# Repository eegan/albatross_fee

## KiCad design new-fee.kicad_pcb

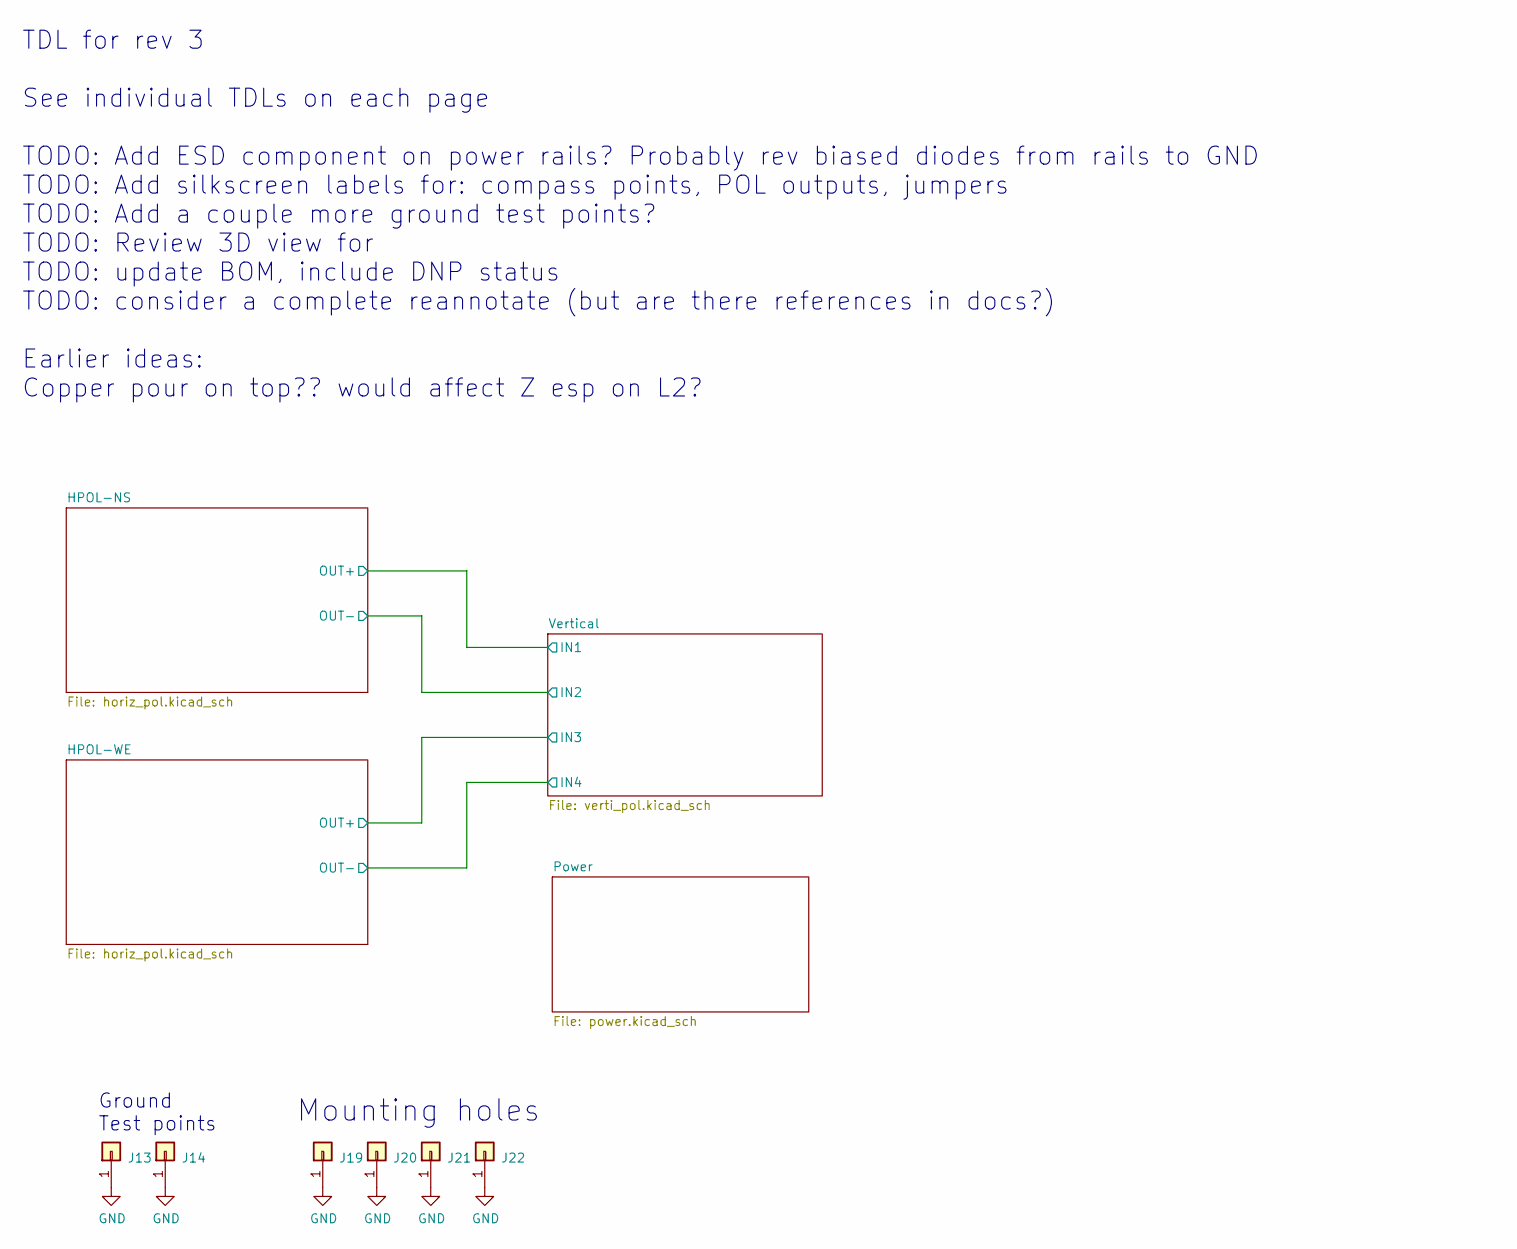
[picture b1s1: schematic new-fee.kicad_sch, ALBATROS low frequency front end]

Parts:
J13, J14: Conn_01x01; PinHeader_1x01_P2.54mm_Vertical
J19, J20, J21, J22: Conn_01x01; MountingHole_2.7mm_M2.5_Pad

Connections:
GND: J13.1, J14.1, J19.1, J20.1, J21.1, J22.1; also elsewhere on the board

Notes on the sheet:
Mounting holes
TDL for rev 3 See individual TDLs on each page TODO: Add ESD component on power rails? Probably rev biased diodes from rails to GND TODO: Add silkscreen labels for: compass points, POL outputs, jumpers TODO: Add a couple more ground test points? TODO: Review 3D view for TODO: update BOM, include DN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
Ground Test points

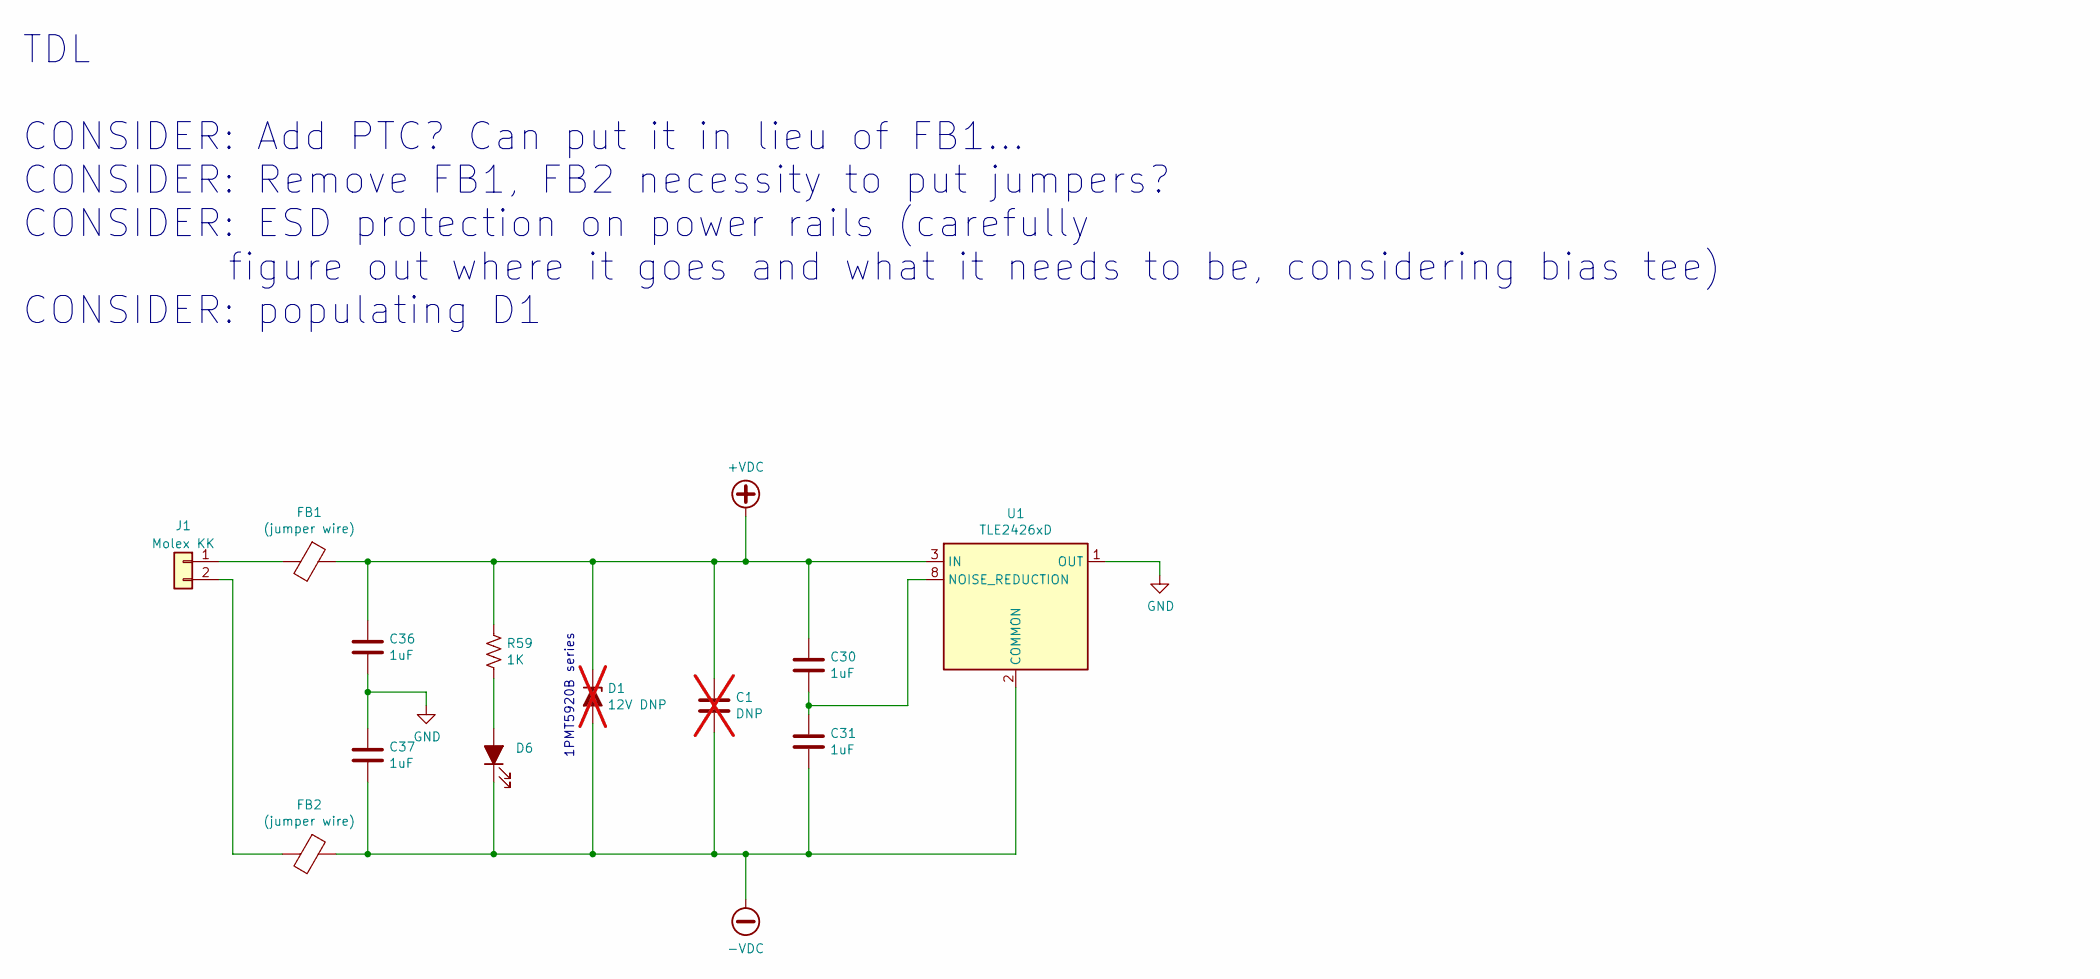
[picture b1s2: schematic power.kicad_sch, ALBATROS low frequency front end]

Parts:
C1: DNP; C_0603_1608Metric; not fitted
C30, C31, C36, C37: 1uF; C_0603_1608Metric; MPN CL10B105KA8NFNC
D1: 12V DNP; D_Powermite_AK; MPN 1PMT5927BT1G; not fitted
D6: LED_ALT; LED_0603_1608Metric; MPN 150060BS75000
FB1, FB2: (jumper wire); R_Axial_DIN0414_L11.9mm_D4.5mm_P25.40mm_Horizontal
J1: Molex KK; Molex_KK-254_AE-6410-02A_1x02_P2.54mm_Vertical; MPN 0022272021
R59: 1K; R_0603_1608Metric
U1: TLE2426xD; SOIC-8_3.9x4.9mm_P1.27mm; MPN TLE2426QDRG4Q1

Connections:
+VDC: C1.1, C30.1, C36.1, D1.1 (K), FB1.1, R59.1, U1.3 (IN); also elsewhere on the board
-VDC: C1.2, C31.2, C37.2, D1.2 (A), D6.1 (K), FB2.1, U1.2 (COMMON); also elsewhere on the board
GND: C36.2, C37.1, U1.1 (OUT); also elsewhere on the board
unnamed: D6.2 (A), R59.2
unnamed: FB1.2, J1.1
unnamed: FB2.2, J1.2
unnamed: C30.2, C31.1, U1.8 (NOISE_REDUCTION)

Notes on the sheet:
TDL CONSIDER: Add PTC? Can put it in lieu of FB1... CONSIDER: Remove FB1, FB2 necessity to put jumpers? CONSIDER: ESD protection on power rails (carefully figure out where it goes and what it needs to be, considering bias tee) CONSIDER: populating D1
1PMT5920B series

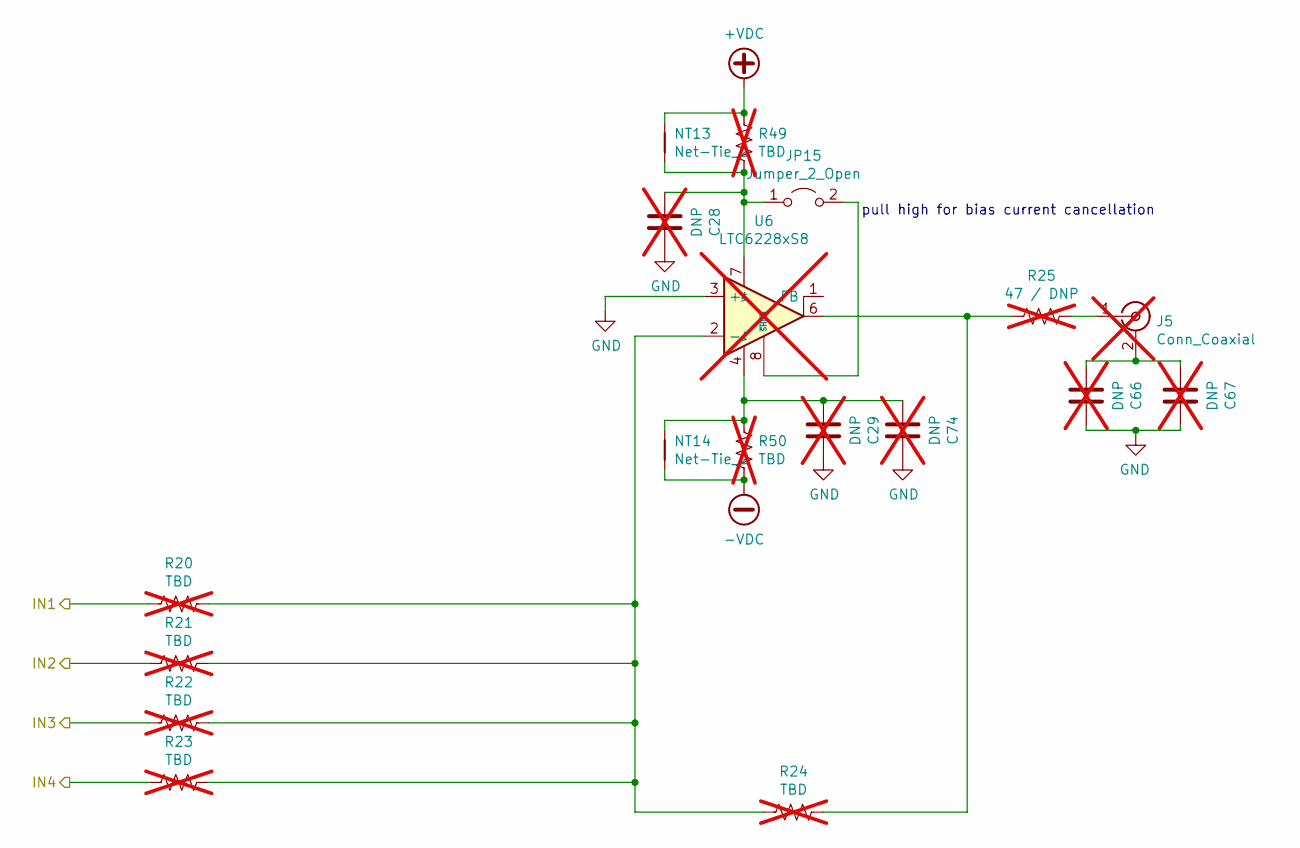
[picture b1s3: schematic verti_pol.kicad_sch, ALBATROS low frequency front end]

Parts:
C28, C29, C66, C67, C74: DNP; C_0603_1608Metric; not fitted
J5: Conn_Coaxial; SMA_Amphenol_901-144_Vertical; MPN 5-1814832-2; not fitted
JP15: Jumper_2_Open; SolderJumper-2_P1.3mm_Open_TrianglePad1.0x1.5mm
NT13, NT14: Net-Tie_2; NetTie-2_SMD_Pad0.5mm
R20, R21, R22, R23, R24, R49, R50: TBD; R_0603_1608Metric; not fitted
R25: 47 / DNP; R_0603_1608Metric; not fitted
U6: LTC6228xS8; SO-8_3.9x4.9mm_P1.27mm; not fitted

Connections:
+VDC: NT13.1, R49.2; also elsewhere on the board
-VDC: NT14.2, R50.1; also elsewhere on the board
/HPOL-NS/OUT+: R20.2; also elsewhere on the board
/HPOL-NS/OUT-: R21.2; also elsewhere on the board
/HPOL-WE/OUT+: R22.2; also elsewhere on the board
/HPOL-WE/OUT-: R23.2; also elsewhere on the board
GND: C28.1, C29.1, C66.1, C67.1, C74.1, U6.3 (+); also elsewhere on the board
unnamed: C29.2, C74.2, NT14.1, R50.2, U6.4 (V-), U6.5 (V-)
unnamed: C66.2, C67.2, J5.2 (Ext)
unnamed: J5.1 (In), R25.1
unnamed: C28.2, JP15.1 (A), NT13.2, R49.1, U6.7 (V+)
unnamed: JP15.2 (B), U6.8 (~SHDN)
unnamed: R24.1, R25.2, U6.6
unnamed: R20.1, R21.1, R22.1, R23.1, R24.2, U6.2 (-)

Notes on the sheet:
pull high for bias current cancellation

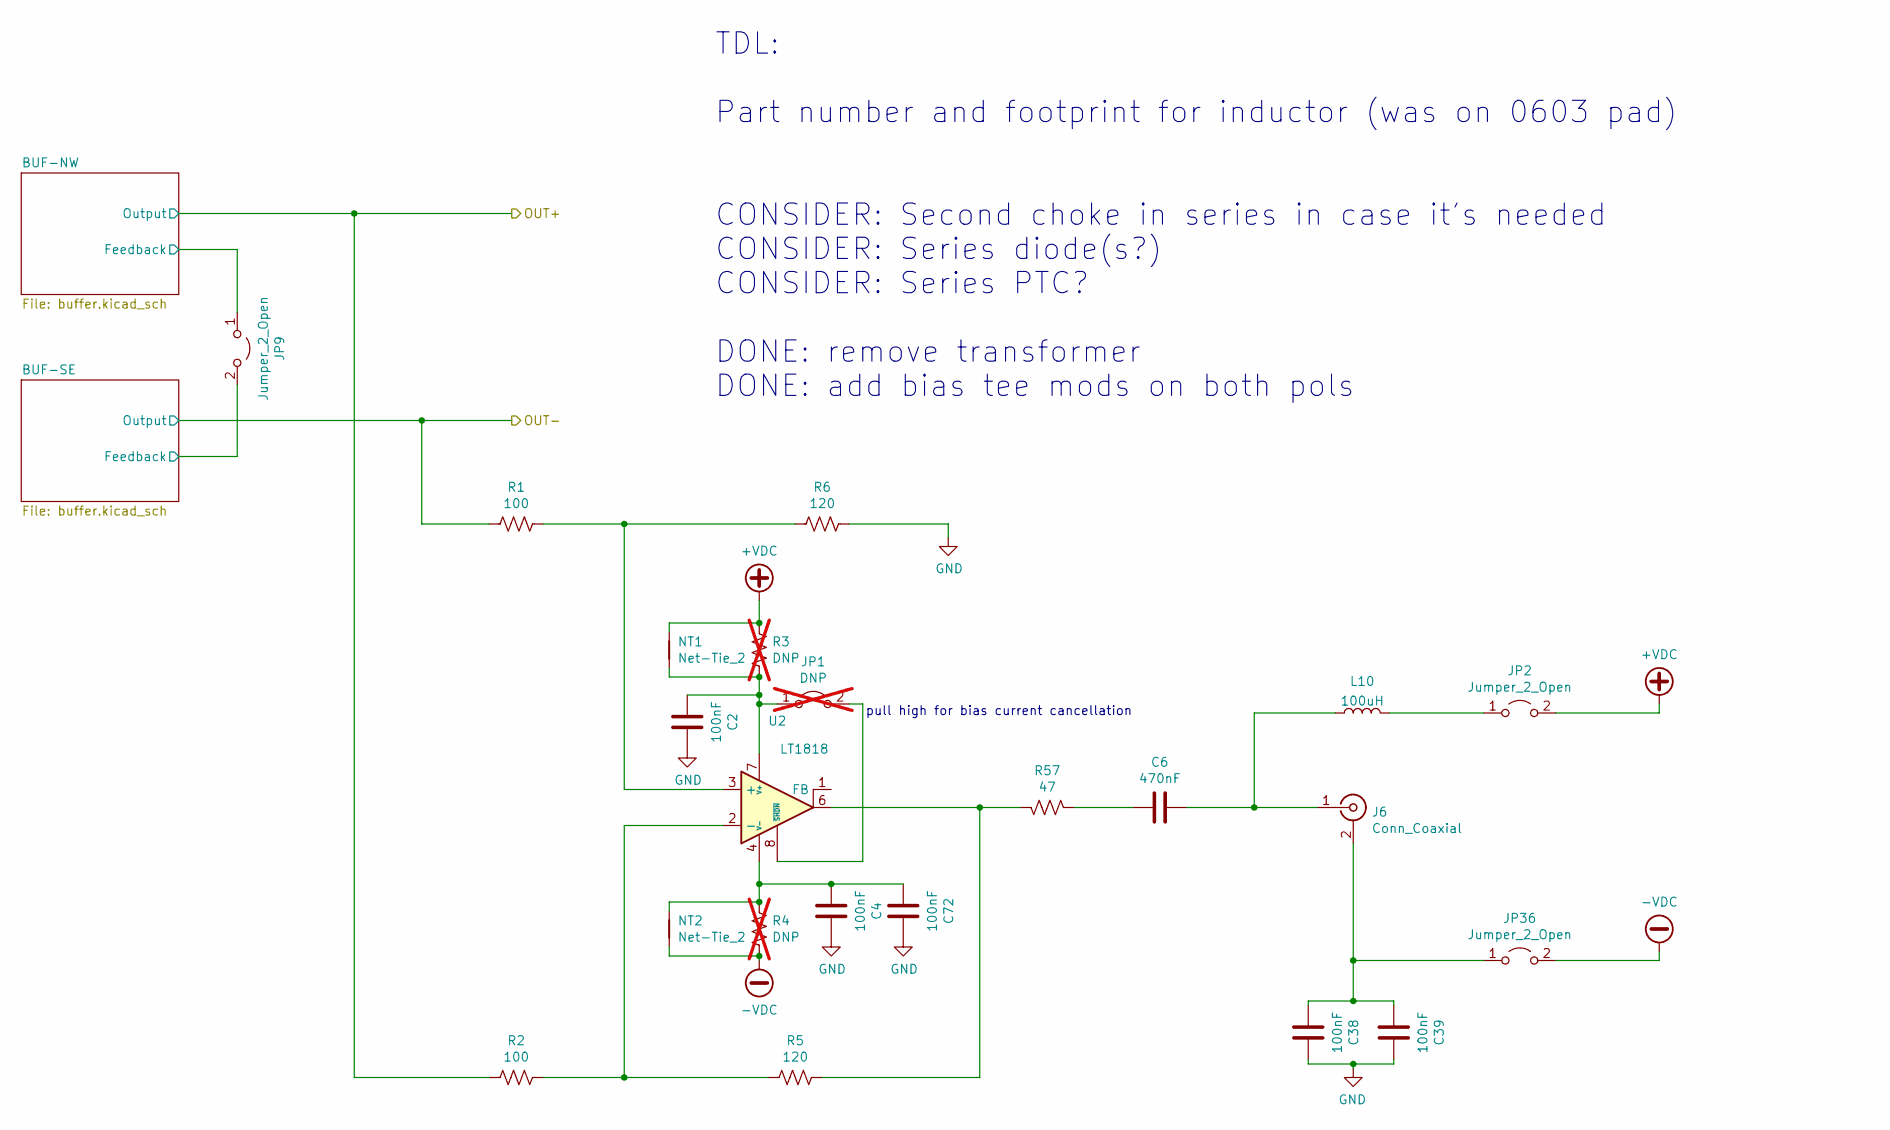
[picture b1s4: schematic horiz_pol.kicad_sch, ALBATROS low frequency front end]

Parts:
C2, C4, C38, C39, C72: 100nF; C_0603_1608Metric; MPN CL10B104KB8NNWC
C6: 470nF; C_0603_1608Metric; MPN CL10B474KA8NFNC
J6: Conn_Coaxial; SMA_Amphenol_901-144_Vertical; MPN 5-1814832-2
JP1: DNP; SolderJumper-2_P1.3mm_Open_TrianglePad1.0x1.5mm; not fitted
JP2, JP9, JP36: Jumper_2_Open; PinHeader_1x02_P2.54mm_Vertical
L10: 100uH; L_0603_1608Metric
NT1, NT2: Net-Tie_2; NetTie-2_SMD_Pad0.5mm
R1, R2: 100; R_0603_1608Metric
R3, R4: DNP; R_0603_1608Metric; not fitted
R5, R6: 120; R_0603_1608Metric
R57: 47; R_0603_1608Metric
U2: LT1818; SO-8_3.9x4.9mm_P1.27mm

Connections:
+VDC: JP2.2 (B), NT1.1, R3.2; also elsewhere on the board
-VDC: JP36.2 (B), NT2.2, R4.1; also elsewhere on the board
/HPOL-NS/BUF-NW/Feedback: JP9.1 (A); also elsewhere on the board
/HPOL-NS/BUF-SE/Feedback: JP9.2 (B); also elsewhere on the board
/HPOL-NS/OUT+: R2.2; also elsewhere on the board
/HPOL-NS/OUT-: R1.2; also elsewhere on the board
GND: C2.1, C4.1, C38.1, C39.1, C72.1, R6.1; also elsewhere on the board
unnamed: C4.2, C72.2, NT2.1, R4.2, U2.4 (V-), U2.5 (V-)
unnamed: C6.2, R57.2
unnamed: C38.2, C39.2, J6.2 (Ext), JP36.1 (A)
unnamed: C6.1, J6.1 (In), L10.1
unnamed: C2.2, JP1.1 (A), NT1.2, R3.1, U2.7 (V+)
unnamed: JP1.2 (B), U2.8 (~SHDN)
unnamed: JP2.1 (A), L10.2
unnamed: R5.1, R57.1, U2.6
unnamed: R1.1, R6.2, U2.3 (+)
unnamed: R2.1, R5.2, U2.2 (-)

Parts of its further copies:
C3: 470nF; C_0603_1608Metric; MPN CL10B474KA8NFNC
C5, C7, C52, C53, C73: 100nF; C_0603_1608Metric; MPN CL10B104KB8NNWC
J2: Conn_Coaxial; SMA_Amphenol_901-144_Vertical; MPN 5-1814832-2
JP3, JP21, JP37: Jumper_2_Open; PinHeader_1x02_P2.54mm_Vertical
JP4: DNP; SolderJumper-2_P1.3mm_Open_TrianglePad1.0x1.5mm; not fitted
L9: 100uH; L_0603_1608Metric
NT3, NT4: Net-Tie_2; NetTie-2_SMD_Pad0.5mm
R7, R8: 100; R_0603_1608Metric
R9, R10: DNP; R_0603_1608Metric; not fitted
R11, R12: 120; R_0603_1608Metric
R58: 47; R_0603_1608Metric
U3: LT1818; SO-8_3.9x4.9mm_P1.27mm

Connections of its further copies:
+VDC: JP3.2 (B), NT3.1, R9.2; also elsewhere on the board
-VDC: JP37.2 (B), NT4.2, R10.1; also elsewhere on the board
/HPOL-WE/BUF-NW/Feedback: JP21.1 (A); also elsewhere on the board
/HPOL-WE/BUF-SE/Feedback: JP21.2 (B); also elsewhere on the board
/HPOL-WE/OUT+: R8.2; also elsewhere on the board
/HPOL-WE/OUT-: R7.2; also elsewhere on the board
GND: C5.1, C7.1, C52.1, C53.1, C73.1, R12.1; also elsewhere on the board
unnamed: C3.2, R58.2
unnamed: C7.2, C73.2, NT4.1, R10.2, U3.4 (V-), U3.5 (V-)
unnamed: C52.2, C53.2, J2.2 (Ext), JP37.1 (A)
unnamed: C3.1, J2.1 (In), L9.1
unnamed: JP3.1 (A), L9.2
unnamed: C5.2, JP4.1 (A), NT3.2, R9.1, U3.7 (V+)
unnamed: JP4.2 (B), U3.8 (~SHDN)
unnamed: R11.1, R58.1, U3.6
unnamed: R7.1, R12.2, U3.3 (+)
unnamed: R8.1, R11.2, U3.2 (-)

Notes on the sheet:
TDL: Part number and footprint for inductor (was on 0603 pad) CONSIDER: Second choke in series in case it's needed CONSIDER: Series diode(s?) CONSIDER: Series PTC? DONE: remove transformer DONE: add bias tee mods on both pols
pull high for bias current cancellation

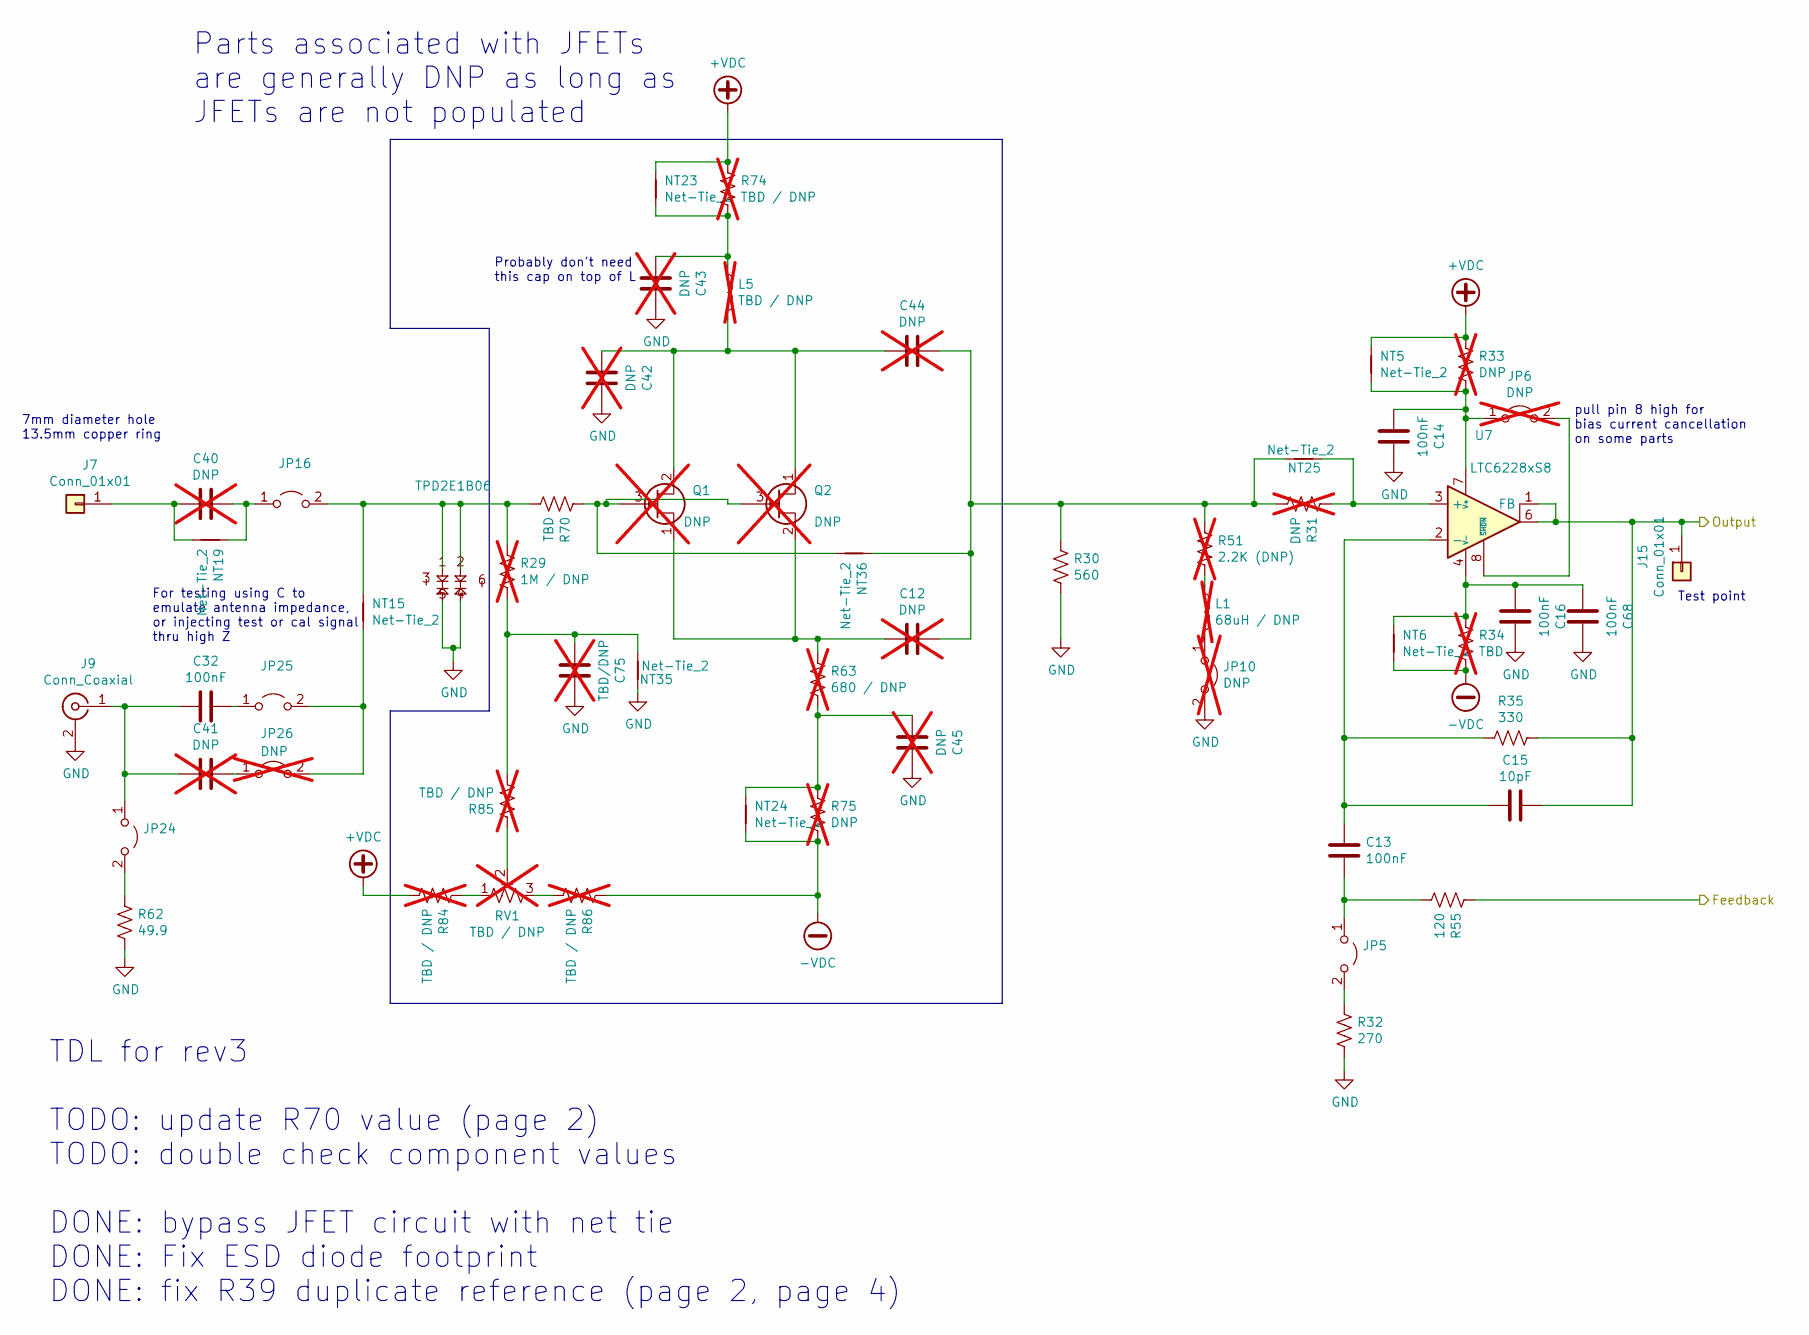
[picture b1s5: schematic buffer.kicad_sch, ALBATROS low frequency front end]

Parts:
C12, C40, C41, C42, C43, C44, C45: DNP; C_0603_1608Metric; not fitted
C13, C14, C16, C32, C68: 100nF; C_0603_1608Metric; MPN CL10B104KB8NNWC
C15: 10pF; C_0603_1608Metric; MPN CL10C100JB8NNNC
C75: TBD/DNP; C_0603_1608Metric; not fitted
D2: TPD2E1B06; SOT-563; MPN TPD2E1B06DRLR
J7: Conn_01x01; MountingHole_7.5mm
J9: Conn_Coaxial; SMA_Amphenol_132289_EdgeMount; MPN CONSMA020.062-G
J15: Conn_01x01; PinHeader_1x01_P2.54mm_Vertical
JP5, JP16, JP24, JP25: Jumper_2_Open; PinHeader_1x02_P2.54mm_Vertical
JP6: DNP; SolderJumper-2_P1.3mm_Open_TrianglePad1.0x1.5mm; not fitted
JP10, JP26: DNP; PinHeader_1x02_P2.54mm_Vertical; not fitted
L1: 68uH / DNP; L_Axial_L6.6mm_D2.7mm_P2.54mm_Vertical_Vishay_IM-2; not fitted
L5: TBD / DNP; L_0603_1608Metric; not fitted
NT5, NT6, NT15, NT19, NT23, NT24, NT25, NT35, NT36: Net-Tie_2; NetTie-2_SMD_Pad0.5mm
Q1, Q2: DNP; SOT-23; not fitted
R29: 1M / DNP; R_0603_1608Metric; not fitted
R30: 560; R_0603_1608Metric
R31, R33, R75: DNP; R_0603_1608Metric; not fitted
R32: 270; R_0603_1608Metric
R34: TBD; R_0603_1608Metric; not fitted
R35: 330; R_0603_1608Metric
R51: 2.2K (DNP); R_0603_1608Metric; not fitted
R55: 120; R_0603_1608Metric
R62: 49.9; R_0603_1608Metric
R63: 680 / DNP; R_0603_1608Metric; not fitted
R70: TBD; R_0603_1608Metric
R74, R84, R85, R86: TBD / DNP; R_0603_1608Metric; not fitted
RV1: TBD / DNP; Potentiometer_Bourns_3386C_Horizontal; not fitted
U7: LTC6228xS8; SO-8_3.9x4.9mm_P1.27mm

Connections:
+VDC: NT5.1, NT23.1, R33.2, R74.2, R84.1; also elsewhere on the board
-VDC: NT6.2, NT24.2, R34.1, R75.1, R86.2; also elsewhere on the board
/HPOL-NS/BUF-NW/Feedback: R55.2; also elsewhere on the board
/HPOL-NS/OUT+: C15.1, J15.1, R35.1, U7.1 (FB), U7.6; also elsewhere on the board
GND: C14.1, C16.1, C42.1, C43.1, C45.1, C68.1, C75.1, D2.4, D2.5, J9.2 (Ext), JP10.2 (B), NT35.1, R30.1, R32.1, R62.1; also elsewhere on the board
unnamed: C12.1, C44.1, NT25.2, NT36.1, R30.2, R31.1, R51.2
unnamed: C16.2, C68.2, NT6.1, R34.2, U7.4 (V-), U7.5 (V-)
unnamed: C43.2, L5.1, NT23.2, R74.1
unnamed: C45.2, NT24.1, R63.1, R75.2
unnamed: C75.2, NT35.2, R29.1, R85.1
unnamed: C40.2, J7.1, NT19.2
unnamed: C32.2, C41.2, J9.1 (In), JP24.1 (A)
unnamed: C13.1, JP5.1 (A), R55.1
unnamed: JP5.2 (B), R32.2
unnamed: C14.2, JP6.1 (A), NT5.2, R33.1, U7.7 (V+)
unnamed: JP6.2 (B), U7.8 (~SHDN)
unnamed: JP10.1 (A), L1.2
unnamed: C40.1, JP16.1 (A), NT19.1
unnamed: D2.1, D2.2, JP16.2 (B), NT15.1, R29.2, R70.1
unnamed: JP24.2 (B), R62.2
unnamed: C32.1, JP25.1 (A)
unnamed: JP25.2 (B), JP26.2 (B), NT15.2
unnamed: C41.1, JP26.1 (A)
unnamed: L1.1, R51.1
unnamed: C42.2, C44.2, L5.2, Q1.2 (D), Q2.1 (D)
unnamed: NT36.2, Q1.3 (G), Q2.3 (G), R70.2
unnamed: C12.2, Q1.1 (S), Q2.2 (S), R63.2
unnamed: R84.2, RV1.1
unnamed: R85.2, RV1.2
unnamed: R86.1, RV1.3
unnamed: NT25.1, R31.2, U7.3 (+)
unnamed: C13.2, C15.2, R35.2, U7.2 (-)

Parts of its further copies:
C8, C17, C23, C46, C47, C48, C49, C50, C51, C54, C55, C56, C57, C58, C59, C60, C61, C62, C63, C64, C65: DNP; C_0603_1608Metric; not fitted
C9, C10, C18, C19, C21, C22, C24, C25, C27, C33, C34, C35, C69, C70, C71: 100nF; C_0603_1608Metric; MPN CL10B104KB8NNWC
C11, C20, C26: 10pF; C_0603_1608Metric; MPN CL10C100JB8NNNC
C76, C77, C78: TBD/DNP; C_0603_1608Metric; not fitted
D3, D4, D5: TPD2E1B06; SOT-563; MPN TPD2E1B06DRLR
J3, J4, J8: Conn_01x01; MountingHole_7.5mm
J10, J11, J12: Conn_Coaxial; SMA_Amphenol_132289_EdgeMount; MPN CONSMA020.062-G
J16, J17, J18: Conn_01x01; PinHeader_1x01_P2.54mm_Vertical
JP7, JP11, JP13, JP17, JP18, JP19, JP27, JP28, JP30, JP31, JP33, JP34: Jumper_2_Open; PinHeader_1x02_P2.54mm_Vertical
JP8, JP12, JP14: DNP; SolderJumper-2_P1.3mm_Open_TrianglePad1.0x1.5mm; not fitted
JP20, JP22, JP23, JP29, JP32, JP35: DNP; PinHeader_1x02_P2.54mm_Vertical; not fitted
L2, L3, L4: 68uH / DNP; L_Axial_L6.6mm_D2.7mm_P2.54mm_Vertical_Vishay_IM-2; not fitted
L6, L7, L8: TBD / DNP; L_0603_1608Metric; not fitted
NT7, NT8, NT9, NT10, NT11, NT12, NT16, NT17, NT18, NT20, NT21, NT22, NT26, NT27, NT28, NT29, NT30, NT31, NT32, NT33, NT34, NT37, NT38, NT39, NT40, NT41, NT42: Net-Tie_2; NetTie-2_SMD_Pad0.5mm
Q3, Q4, Q5, Q6, Q7, Q8: DNP; SOT-23; not fitted
R14, R27, R37: 1M / DNP; R_0603_1608Metric; not fitted
R15, R36, R38: 560; R_0603_1608Metric
R16, R18, R39, R41, R44, R46, R77, R79, R81: DNP; R_0603_1608Metric; not fitted
R17, R40, R45: 270; R_0603_1608Metric
R19, R42, R47: TBD; R_0603_1608Metric; not fitted
R26, R43, R48: 330; R_0603_1608Metric
R52, R53, R54: 2.2K (DNP); R_0603_1608Metric; not fitted
R56, R82, R83: 120; R_0603_1608Metric
R64, R66, R68: 49.9; R_0603_1608Metric
R65, R67, R69: 680 / DNP; R_0603_1608Metric; not fitted
R71, R72, R73: TBD; R_0603_1608Metric
R76, R78, R80, R87, R88, R89, R90, R91, R92, R93, R94, R95: TBD / DNP; R_0603_1608Metric; not fitted
RV2, RV3, RV4: TBD / DNP; Potentiometer_Bourns_3386C_Horizontal; not fitted
U4, U5, U8: LTC6228xS8; SO-8_3.9x4.9mm_P1.27mm

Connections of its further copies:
+VDC: NT7.1, NT9.1, NT11.1, NT26.1, NT29.1, NT32.1, R18.2, R41.2, R46.2, R76.2, R78.2, R80.2, R87.1, R90.1, R93.1; also elsewhere on the board
-VDC: NT8.2, NT10.2, NT12.2, NT27.2, NT30.2, NT33.2, R19.1, R42.1, R47.1, R77.1, R79.1, R81.1, R89.2, R92.2, R95.2; also elsewhere on the board
/HPOL-NS/BUF-SE/Feedback: R56.2; also elsewhere on the board
/HPOL-NS/OUT-: C20.1, J16.1, R43.1, U8.1 (FB), U8.6; also elsewhere on the board
/HPOL-WE/BUF-NW/Feedback: R82.2; also elsewhere on the board
/HPOL-WE/BUF-SE/Feedback: R83.2; also elsewhere on the board
/HPOL-WE/OUT+: C11.1, J17.1, R26.1, U4.1 (FB), U4.6; also elsewhere on the board
/HPOL-WE/OUT-: C26.1, J18.1, R48.1, U5.1 (FB), U5.6; also elsewhere on the board
GND: C10.1, C19.1, C21.1, C22.1, C25.1, C27.1, C48.1, C49.1, C51.1, C56.1, C57.1, C59.1, C62.1, C63.1, C65.1, C69.1, C70.1, C71.1, C76.1, C77.1, C78.1, D3.4, D3.5, D4.4, D4.5, D5.4, D5.5, J10.2 (Ext), J11.2 (Ext), J12.2 (Ext), JP20.2 (B), JP22.2 (B), JP23.2 (B), NT37.1, NT39.1, NT41.1, R15.1, R17.1, R36.1, R38.1, R40.1, R45.1, R64.1, R66.1, R68.1; also elsewhere on the board
unnamed: C17.1, C50.1, NT28.2, NT40.1, R38.2, R39.1, R52.2
unnamed: C21.2, C69.2, NT8.1, R42.2, U8.4 (V-), U8.5 (V-)
unnamed: C22.2, C70.2, NT10.1, R19.2, U4.4 (V-), U4.5 (V-)
unnamed: C23.1, C64.1, NT34.2, NT42.1, R36.2, R44.1, R54.2
unnamed: C27.2, C71.2, NT12.1, R47.2, U5.4 (V-), U5.5 (V-)
unnamed: C49.2, L6.1, NT26.2, R76.1
unnamed: C51.2, NT27.1, R65.1, R77.2
unnamed: C57.2, L7.1, NT29.2, R78.1
unnamed: C8.1, C58.1, NT31.2, NT38.1, R15.2, R16.1, R53.2
unnamed: C59.2, NT30.1, R67.1, R79.2
unnamed: C63.2, L8.1, NT32.2, R80.1
unnamed: C65.2, NT33.1, R69.1, R81.2
unnamed: C76.2, NT37.2, R37.1, R88.1
unnamed: C77.2, NT39.2, R14.1, R91.1
unnamed: C78.2, NT41.2, R27.1, R94.1
unnamed: C54.2, J3.1, NT21.2
unnamed: C60.2, J4.1, NT22.2
unnamed: C46.2, J8.1, NT20.2
unnamed: C33.2, C47.2, J10.1 (In), JP27.1 (A)
unnamed: C34.2, C55.2, J11.1 (In), JP30.1 (A)
unnamed: C35.2, C61.2, J12.1 (In), JP33.1 (A)
unnamed: C18.1, JP7.1 (A), R56.1
unnamed: JP7.2 (B), R40.2
unnamed: C19.2, JP8.1 (A), NT7.2, R41.1, U8.7 (V+)
unnamed: JP8.2 (B), U8.8 (~SHDN)
unnamed: C9.1, JP11.1 (A), R82.1
unnamed: JP11.2 (B), R17.2
unnamed: C10.2, JP12.1 (A), NT9.2, R18.1, U4.7 (V+)
unnamed: JP12.2 (B), U4.8 (~SHDN)
unnamed: C24.1, JP13.1 (A), R83.1
unnamed: JP13.2 (B), R45.2
unnamed: C25.2, JP14.1 (A), NT11.2, R46.1, U5.7 (V+)
unnamed: JP14.2 (B), U5.8 (~SHDN)
unnamed: C46.1, JP17.1 (A), NT20.1
unnamed: D3.1, D3.2, JP17.2 (B), NT16.1, R37.2, R71.1
unnamed: C54.1, JP18.1 (A), NT21.1
unnamed: D4.1, D4.2, JP18.2 (B), NT17.1, R14.2, R72.1
unnamed: C60.1, JP19.1 (A), NT22.1
unnamed: D5.1, D5.2, JP19.2 (B), NT18.1, R27.2, R73.1
unnamed: JP20.1 (A), L2.2
unnamed: JP22.1 (A), L3.2
unnamed: JP23.1 (A), L4.2
unnamed: JP27.2 (B), R64.2
unnamed: C33.1, JP28.1 (A)
unnamed: JP28.2 (B), JP29.2 (B), NT16.2
unnamed: C47.1, JP29.1 (A)
unnamed: JP30.2 (B), R66.2
unnamed: C34.1, JP31.1 (A)
unnamed: JP31.2 (B), JP32.2 (B), NT17.2
unnamed: C55.1, JP32.1 (A)
unnamed: JP33.2 (B), R68.2
unnamed: C35.1, JP34.1 (A)
unnamed: JP34.2 (B), JP35.2 (B), NT18.2
unnamed: C61.1, JP35.1 (A)
unnamed: L2.1, R52.1
unnamed: L3.1, R53.1
unnamed: L4.1, R54.1
unnamed: C48.2, C50.2, L6.2, Q3.2 (D), Q4.1 (D)
unnamed: NT40.2, Q3.3 (G), Q4.3 (G), R71.2
unnamed: C17.2, Q3.1 (S), Q4.2 (S), R65.2
unnamed: C56.2, C58.2, L7.2, Q5.2 (D), Q6.1 (D)
unnamed: NT38.2, Q5.3 (G), Q6.3 (G), R72.2
unnamed: C8.2, Q5.1 (S), Q6.2 (S), R67.2
unnamed: C62.2, C64.2, L8.2, Q7.2 (D), Q8.1 (D)
unnamed: NT42.2, Q7.3 (G), Q8.3 (G), R73.2
unnamed: C23.2, Q7.1 (S), Q8.2 (S), R69.2
unnamed: R87.2, RV2.1
unnamed: R88.2, RV2.2
unnamed: R89.1, RV2.3
unnamed: R90.2, RV3.1
unnamed: R91.2, RV3.2
unnamed: R92.1, RV3.3
unnamed: R93.2, RV4.1
unnamed: R94.2, RV4.2
unnamed: R95.1, RV4.3
unnamed: NT31.1, R16.2, U4.3 (+)
unnamed: C9.2, C11.2, R26.2, U4.2 (-)
unnamed: NT34.1, R44.2, U5.3 (+)
unnamed: C24.2, C26.2, R48.2, U5.2 (-)
unnamed: NT28.1, R39.2, U8.3 (+)
unnamed: C18.2, C20.2, R43.2, U8.2 (-)

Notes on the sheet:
Test point
Parts associated with JFETs are generally DNP as long as JFETs are not populated
TDL for rev3 TODO: update R70 value (page 2) TODO: double check component values DONE: bypass JFET circuit with net tie DONE: Fix ESD diode footprint DONE: fix R39 duplicate reference (page 2, page 4)
pull pin 8 high for bias current cancellation on some parts
For testing using C to emulate antenna impedance, or injecting test or cal signal thru high Z
Probably don't need this cap on top of L
7mm diameter hole 13.5mm copper ring

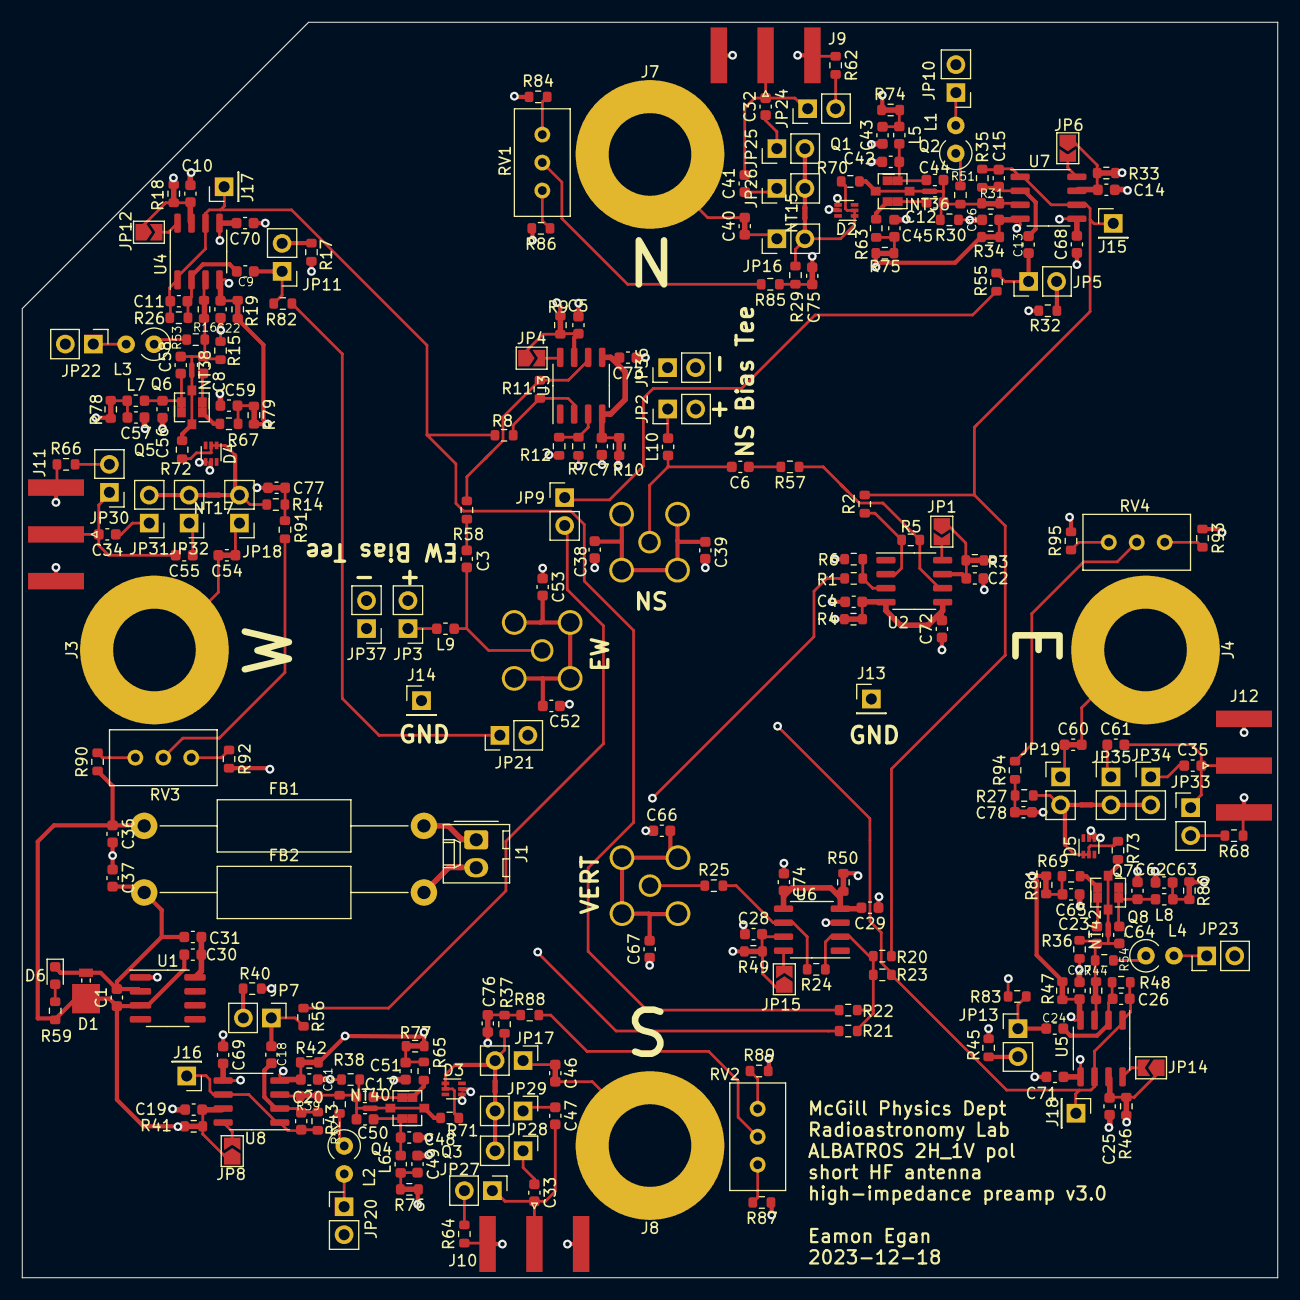
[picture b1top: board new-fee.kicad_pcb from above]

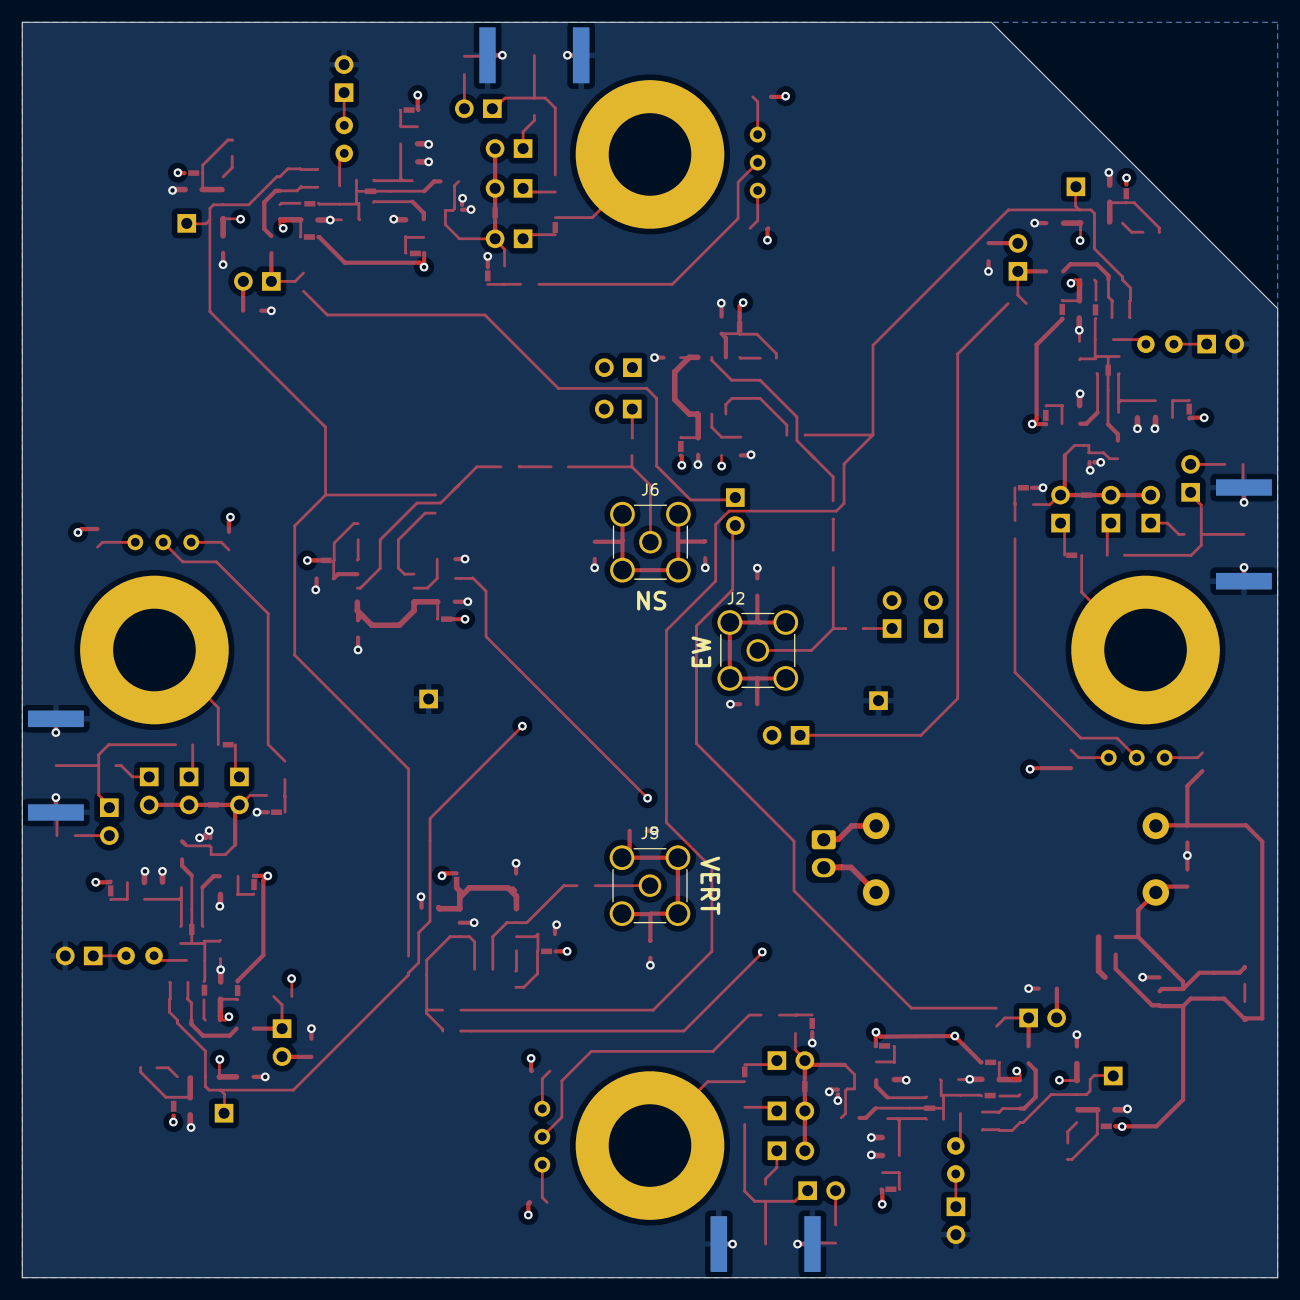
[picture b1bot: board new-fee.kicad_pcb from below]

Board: 4 copper layers, 114.0 x 114.0 mm, 304 parts (3 on the bottom side), 150 nets.

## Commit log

2021-05-15 Initial commit - of initial sketch
2021-05-16 Complete rough structure and most aspects of schematic level design
2021-05-16 Add input AM BCB filter
2021-05-16 annotate; connect feedback pins
2021-05-16 Add board outline with locations of holes
2021-05-16 Add most footprints for size trial (looking at parts on PCB)
2021-05-17 Add footprints (not necessarily final)
2021-05-17 Place and route buffer section
2021-05-18 trial use of replicate layout
2021-05-18 Add jumpers, make them pin jumpers
2021-05-18 Finish routing h-pol, before trying to duplicate layout and see if there are shorts
2021-05-19 Routing all done
2021-05-21 Test points added at output of each leg preamp. Mounting holes added. As ordered v1.0b
2021-11-03 Stuff as found in the folder before starting rev2. I guess I didn't commit them earlier
2021-11-04 1st stage schematic change: Add 50Ω termination with jumper at SMA Add 2 capacitors with jumpers between SMA and input Add capacitor and jumper between antenna and input Add JFET (two pinouts, with t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
2021-11-04 Float the horizontal pol SMA ground Mostly notes and minor edits on Buffer.sch
2021-11-05 horiz_pol, verti-pol: Add coupling capacitors on output buffer: mostly text changes pcb: new buffer ckt pretty much routed, before some changes to feedback pin etc
2021-11-05 Prior to testing replicate layout Connected FB pin Changed block names to indicate compass points Tore up nets we're going to route on internal layers
2021-11-06 inter-block routing and power traces deleted board setup changed to 4 layers prior to replicate layout step (for real this time)
2021-11-06 a bit more trace cleanup see zero-pad nets, going to update from sch or try other things
2021-11-11 Fully routed still need to adjust hole location, add back mounting holes and text
2021-11-19 Add TDL notes
2021-11-22 Add bias pot, adjust antenna hole diameter and position (make them exactly 90mm apart)
2021-11-24 Rev 2 PCBs as ordered (fee_v2a_gerber.zip)
2022-06-14 Commit KiCAD 6.0 versions of all the files No substantive changes thought to have been made Also committed eco.txt, .gitignore with a few more extensions
2022-06-27 Update components to as-built state. Add graphic lines to show bias tee mod.
2023-12-18 mostly git 6 to git 7?, some text cleaned up?
2023-12-18 update schematic drawing control block
2023-12-18 change rev 1 to 2 in title block
2023-12-18 make schematic changes for most TODO items; update TDL
2023-12-18 fix duplicate resistor name R55 was wrongly changed to R39??; complete schematic annotation
2023-12-18 minor sch edits prior to implementing changes; implement changes on pcb
2023-12-18 deleted v5 schematic files
2023-12-20 DRC errors checked, trace clearance lowered from 0.2mm to 0.15mm
2023-12-21 Add DNP designations to parts on schematic. Add silkscreen text indications on PCB. Fix some, check other DRC errors.
2023-12-21 Populate parts list. Change power connector to proper Molex footprint.
2024-01-18 bom field completions
2024-01-18 a few parts attribute changes
